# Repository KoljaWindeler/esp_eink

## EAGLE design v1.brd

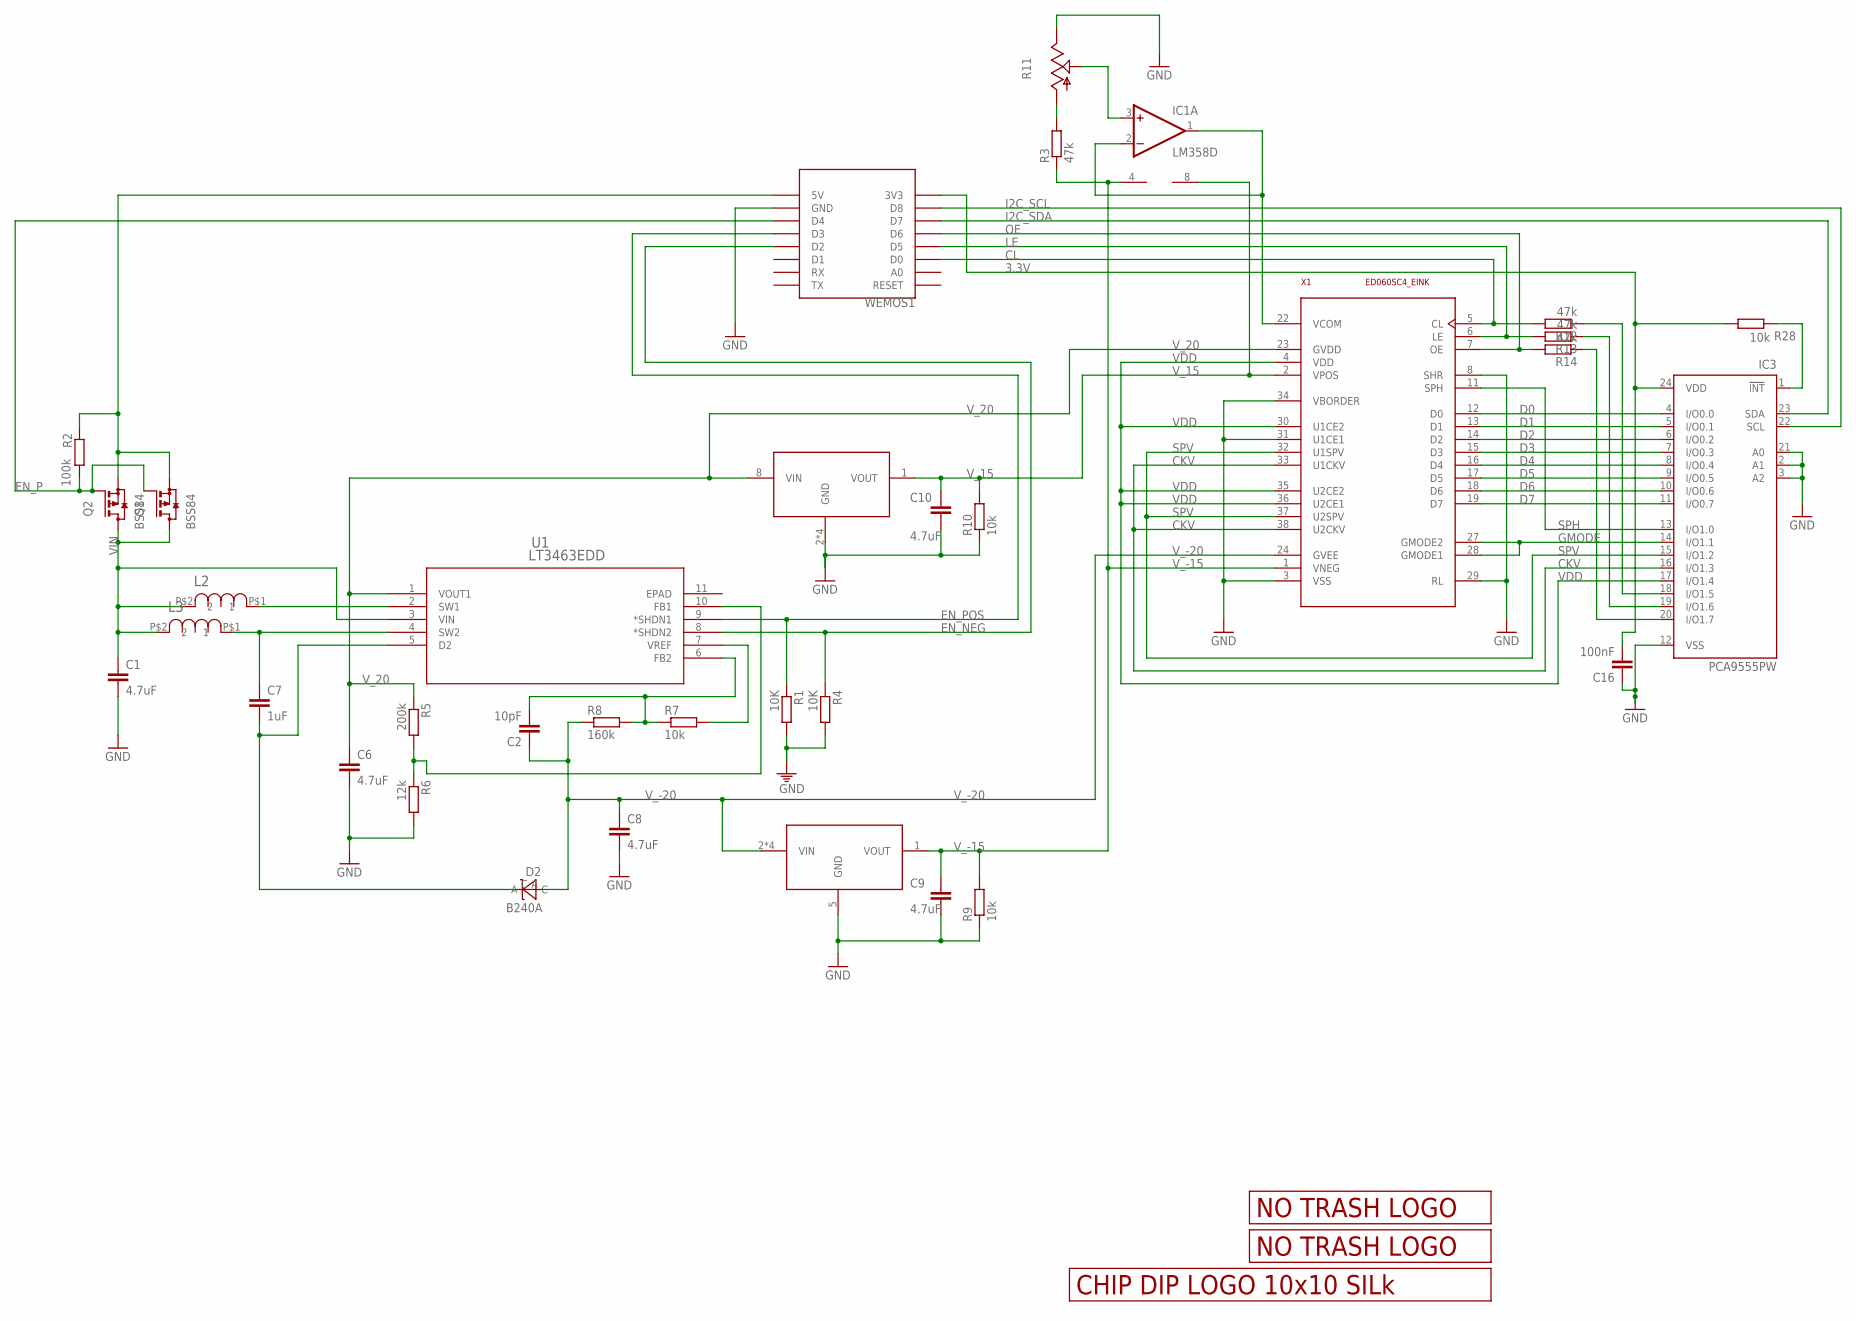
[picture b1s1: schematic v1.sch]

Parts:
C1, C6, C8, C9, C10: 4.7uF; C0805
C2: 10pF; C0805
C7: 1uF; C0805
C16: 100nF; C0805
D2: B240A; DO-214AC
IC1: LM358D; SO08
IC3: PCA9555PW; TSSOP24
L2, L3: SRN6045-100M; SRN6045
Q1, Q2: BSS84; SOT23
R1, R4: 10K; M0805
R2: 100k; R0805
R3, R12, R13, R14: 47k; M0805
R5: 200k; M0805
R6: 12k; M0805
R7, R9, R10, R28: 10k; M0805
R8: 160k; M0805
R11: TRIM_US-SM-42/43X; SM-42/43X
U1: LT3463EDD; DFN-10_DD
U$1: LM78L15ACMX; SOIC127P600X175-8N
U$2: LM79L15ACDG; SOIC127P600X175-8N
U$3: LOGO_10X10_SILK; LOGO2_10X10_SILK
U$4: LOGO_NO_TRASHNO_TRASH; LOGO_ROHS_NO_TRASH
U$5: LOGO_NO_TRASHROHS; LOGO_ROHS_SYM
WEMOS1: WEMOS-D1-MINI
X1: ED060SC4_EINK; FH26-39S-0.3SHW

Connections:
3.3V: C16.2, IC3.24 (VDD), R28.2, WEMOS1.3V3
CKV: IC3.16 (I/O1.3), X1.33 (U1CKV), X1.38 (U2CKV)
CL: R12.2, WEMOS1.D0, X1.5 (CL)
D0: IC3.4 (I/O0.0), X1.12 (D0)
D1: IC3.5 (I/O0.1), X1.13 (D1)
D2: IC3.6 (I/O0.2), X1.14 (D2)
D3: IC3.7 (I/O0.3), X1.15 (D3)
D4: IC3.8 (I/O0.4), X1.16 (D4)
D5: IC3.9 (I/O0.5), X1.17 (D5)
D6: IC3.10 (I/O0.6), X1.18 (D6)
D7: IC3.11 (I/O0.7), X1.19 (D7)
EN_NEG: R4.1, U1.8 (*SHDN2), WEMOS1.D2
EN_P: Q1.1 (G), Q2.1 (G), R2.1, WEMOS1.D4
EN_POS: R1.1, U1.9 (*SHDN1), WEMOS1.D3
GMODE: IC3.14 (I/O1.1), X1.27 (GMODE2), X1.28 (GMODE1)
GND: C1.2, C6.2, C8.2, C9.2, C10.2, C16.1, IC3.2 (A1), IC3.3 (A2), IC3.12 (VSS), IC3.21 (A0), R1.2, R4.2, R6.2, R9.1, R10.1, R11.3 (E), U$1.2 (GND), U$1.3 (GND), U$1.6 (GND), U$1.7 (GND), U$2.5 (GND), WEMOS1.GND, X1.3 (VSS), X1.8 (SHR), X1.29 (RL), X1.31 (U1CE1), X1.34 (VBORDER)
I2C_SCL: IC3.22 (SCL), WEMOS1.D8
I2C_SDA: IC3.23 (SDA), WEMOS1.D7
KPD_INT: IC3.1 (!INT), R28.1
LE: R13.2, WEMOS1.D5, X1.6 (LE)
unnamed: L2.P$1 (1), U1.2 (SW1)
unnamed: C7.1, L3.P$1 (1), U1.4 (SW2)
unnamed: R5.2, R6.1, U1.10 (FB1)
unnamed: C7.2, D2.C, U1.5 (D2)
unnamed: C2.2, R7.1, R8.2, U1.6 (FB2)
unnamed: R7.2, U1.7 (VREF)
unnamed: IC1.1 (OUT), IC1.2 (-IN), X1.22 (VCOM)
unnamed: Q1.2 (S), Q2.2 (S), R2.2, WEMOS1.5V
unnamed: R3.2, R11.1 (A)
unnamed: IC1.3 (+IN), R11.2 (S)
unnamed: IC3.20 (I/O1.7), R14.1
unnamed: IC3.19 (I/O1.6), R13.1
unnamed: IC3.18 (I/O1.5), R12.1
OE: R14.2, WEMOS1.D6, X1.7 (OE)
SPH: IC3.13 (I/O1.0), X1.11 (SPH)
SPV: IC3.15 (I/O1.2), X1.32 (U1SPV), X1.37 (U2SPV)
VDD: IC3.17 (I/O1.4), X1.4 (VDD), X1.30 (U1CE2), X1.35 (U2CE2), X1.36 (U2CE1)
VIN: C1.1, L2.P$2 (2), L3.P$2 (2), Q1.3 (D), Q2.3 (D), U1.3 (VIN)
V_15: C10.1, IC1.8 (V+), R10.2, U$1.1 (VOUT), X1.2 (VPOS)
V_20: C6.1, R5.1, U1.1 (VOUT1), U$1.8 (VIN), X1.23 (GVDD)
V_-15: C9.1, IC1.4 (V-), R3.1, R9.2, U$2.1 (VOUT), X1.1 (VNEG)
V_-20: C2.1, C8.1, D2.A, R8.1, U$2.2 (VIN), U$2.3 (VIN), U$2.6 (VIN), U$2.7 (VIN), X1.24 (GVEE)

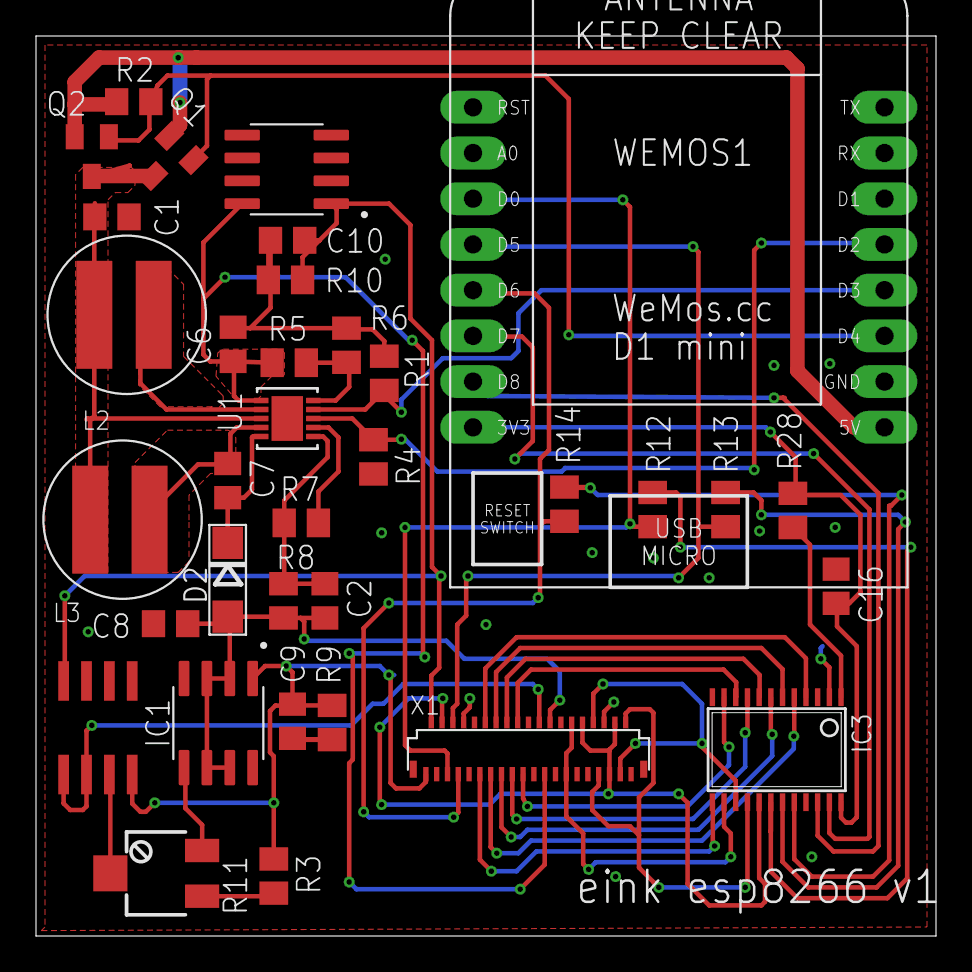
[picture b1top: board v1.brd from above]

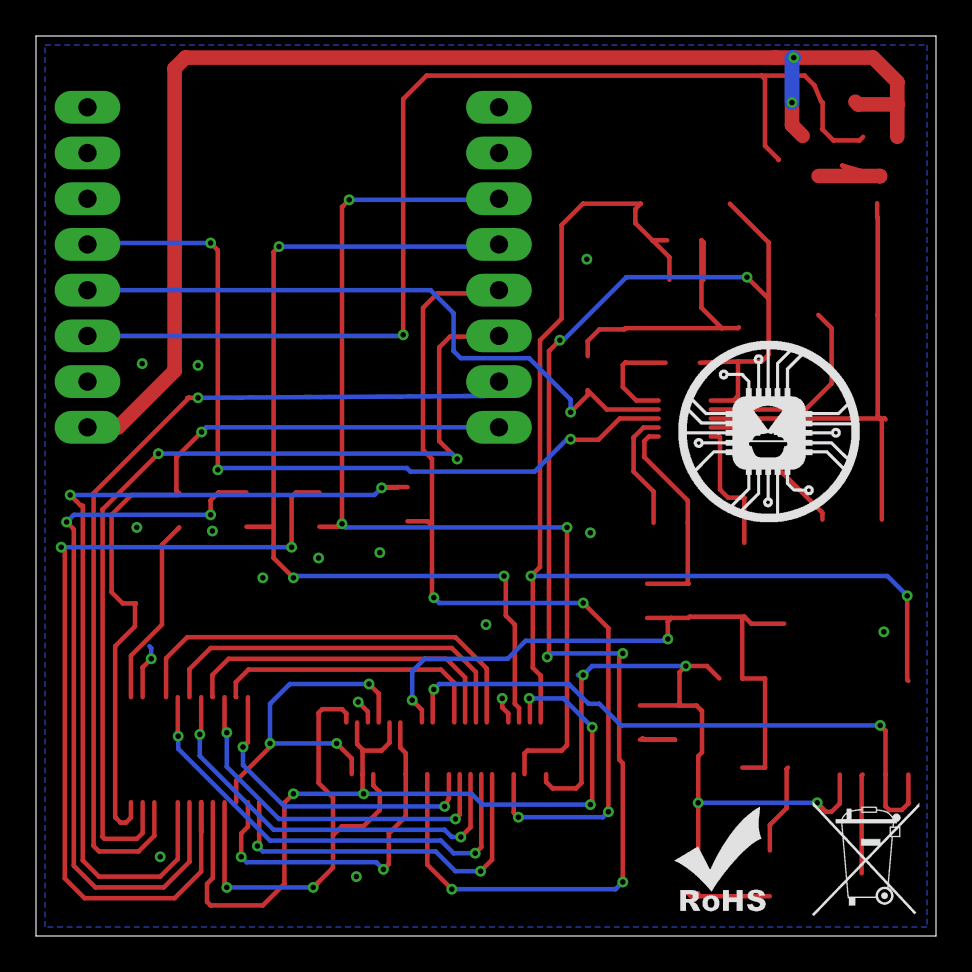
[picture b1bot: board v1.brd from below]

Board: 2 copper layers, 50.0 x 50.0 mm, 38 parts (3 on the bottom side), 42 nets.

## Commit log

2017-12-22 init
2017-12-22 docu
2017-12-23 added php converter

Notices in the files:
parts and their libraries:
JKW_CHIP: License : http://creativecommons.org/licenses/by-sa/3.0
(Creative Commons 3.0)
